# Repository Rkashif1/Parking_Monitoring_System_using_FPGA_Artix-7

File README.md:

# Parking Monitoring System Using FPGA (Artix-7)/PCB Designing

This project demonstrates a **Parking Monitoring System** implemented on an Artix-7 FPGA, designed to monitor parking spot occupancy and ensure safe parking operations. Using ultrasonic and infrared sensors, the system detects vehicle presence in each spot, with real-time status updates displayed on 7-segment displays and collision warnings triggered by a buzzer.

## Project Overview

The Parking Monitoring System leverages FPGA technology for real-time detection and monitoring of parking spaces. The FPGA processes data from multiple sensors to determine spot occupancy and prevent potential collisions. The system’s status is displayed in real-time, providing clear and accurate information on parking availability.

## Features

- **Real-Time Spot Monitoring:** Ultrasonic and infrared sensors track each parking spot’s occupancy, ensuring immediate detection of parked or vacant spaces.
- **Collision Warning System:** A buzzer alerts users to potential collisions, enhancing safety.
- **7-Segment Display for Status Updates:** Real-time parking status is displayed on multiple 7-segment displays, showing each spot’s availability.
- **Custom PCB-Level FPGA Peripheral Board:** A custom PCB board was specifically created for this project, providing a streamlined interface to connect sensors and displays directly to the FPGA. This board facilitates efficient data handling and output control, ensuring robust system performance.

## Hardware Components

- **Artix-7 FPGA:** The main controller, processing sensor inputs and managing display and buzzer outputs.
- **Ultrasonic Sensors:** Detect vehicles within parking spots, identifying occupancy.
- **Infrared Sensors:** Used for accurate vehicle detection and collision prevention.
- **7-Segment Displays:** Show each parking spot’s availability status in real-time.
- **Buzzer:** Provides an audible alert to warn against potential collisions.
- **Custom PCB Peripheral Board:** Created specifically for this project to interface the FPGA with sensors and displays, ensuring efficient data flow and control.

## Setup and Usage

1. **Hardware Setup:** Assemble the custom PCB with ultrasonic and infrared sensors connected to the Artix-7 FPGA. Configure connections to 7-segment displays and the buzzer on the PCB.
2. **FPGA Programming:** Upload the VHDL code to the FPGA for processing sensor inputs and managing output displays.
3. **Testing:** Run tests to verify real-time status display, spot detection, and collision warnings.
4. **Deployment:** Implement the system in a model parking lot setup to simulate real-world operations.

## Future Enhancements

- Integrate more advanced collision avoidance algorithms.
- Develop a mobile app to remotely monitor parking availability.
- Expand the system to manage larger parking structures.

## Team Collaboration

Each team member contributed to FPGA programming, PCB design, and sensor integration. Collaborative development ensured a robust and reliable parking monitoring solution with clear, real-time display and alerts.

## Conclusion

The Parking Monitoring System Using FPGA (Artix-7) demonstrates the use of FPGA for precise and real-time monitoring of parking spaces. With a custom PCB peripheral board specifically created for this project, collision warnings, and clear display output, this system enhances parking efficiency and safety.

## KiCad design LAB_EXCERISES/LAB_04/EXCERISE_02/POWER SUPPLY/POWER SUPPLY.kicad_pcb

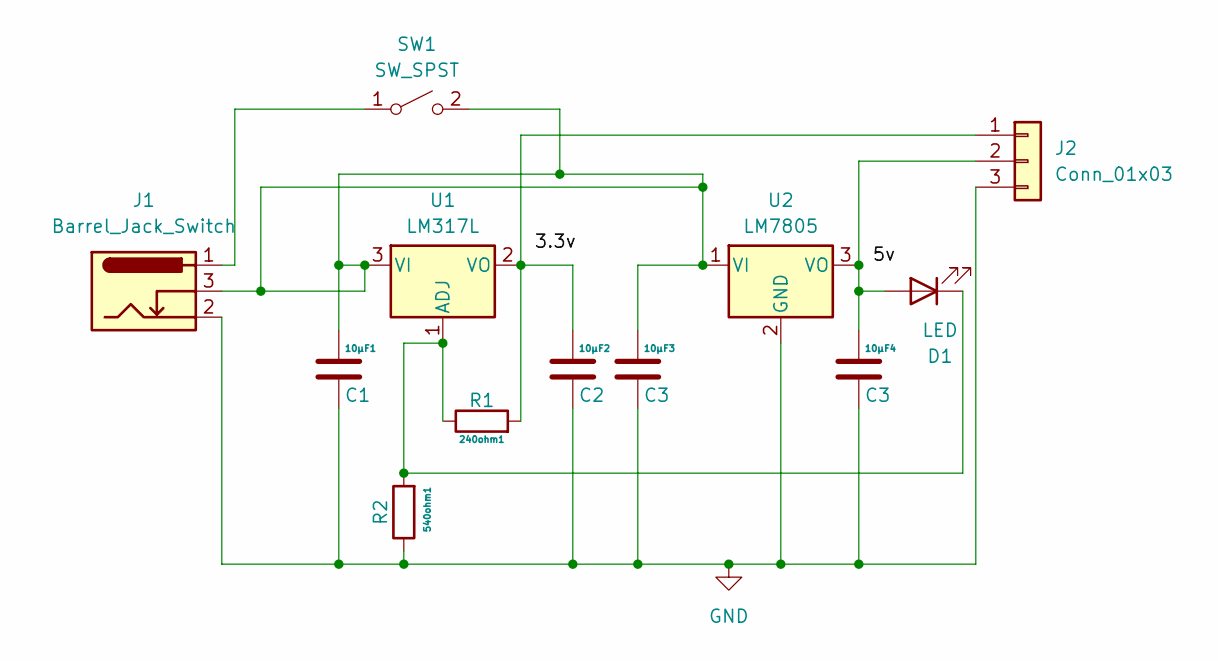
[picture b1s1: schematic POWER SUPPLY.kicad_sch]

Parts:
10µF1: C1; CP_Radial_D5.0mm_P2.00mm
10µF2: C2; CP_Radial_D5.0mm_P2.00mm
10µF3, 10µF4: C3; CP_Radial_D5.0mm_P2.00mm
240ohm1: R1; R_Axial_DIN0204_L3.6mm_D1.6mm_P5.08mm_Horizontal
540ohm1: R2; R_Axial_DIN0204_L3.6mm_D1.6mm_P5.08mm_Horizontal
D1: LED; LED_D5.0mm-4_RGB_Staggered_Pins
J1: Barrel_Jack_Switch; BarrelJack_Horizontal
J2: Conn_01x03; PinHeader_1x03_P1.00mm_Vertical
SW1: SW_SPST; SW_SPST_Omron_B3F-315x_Angled
U1: LM317L; SOT-89-3
U2: LM7805; TO-220-3_Vertical

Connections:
GND: 10µF1.2, 10µF2.2, 10µF3.2, 10µF4.2, 540ohm1.1, J1.2, J2.3, U2.2 (GND)
unnamed: 10µF4.1, D1.2 (A), J2.2, U2.3 (VO)
unnamed: 240ohm1.1, 540ohm1.2, D1.1 (K), U1.1 (ADJ)
unnamed: 10µF2.1, 240ohm1.2, J2.1, U1.2 (VO)
unnamed: J1.1, SW1.1 (A)
unnamed: 10µF1.1, 10µF3.1, J1.3, SW1.2 (B), U1.3 (VI), U2.1 (VI)

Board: 2 copper layers, 12 parts (0 on the bottom side), 6 nets, no tracks yet.

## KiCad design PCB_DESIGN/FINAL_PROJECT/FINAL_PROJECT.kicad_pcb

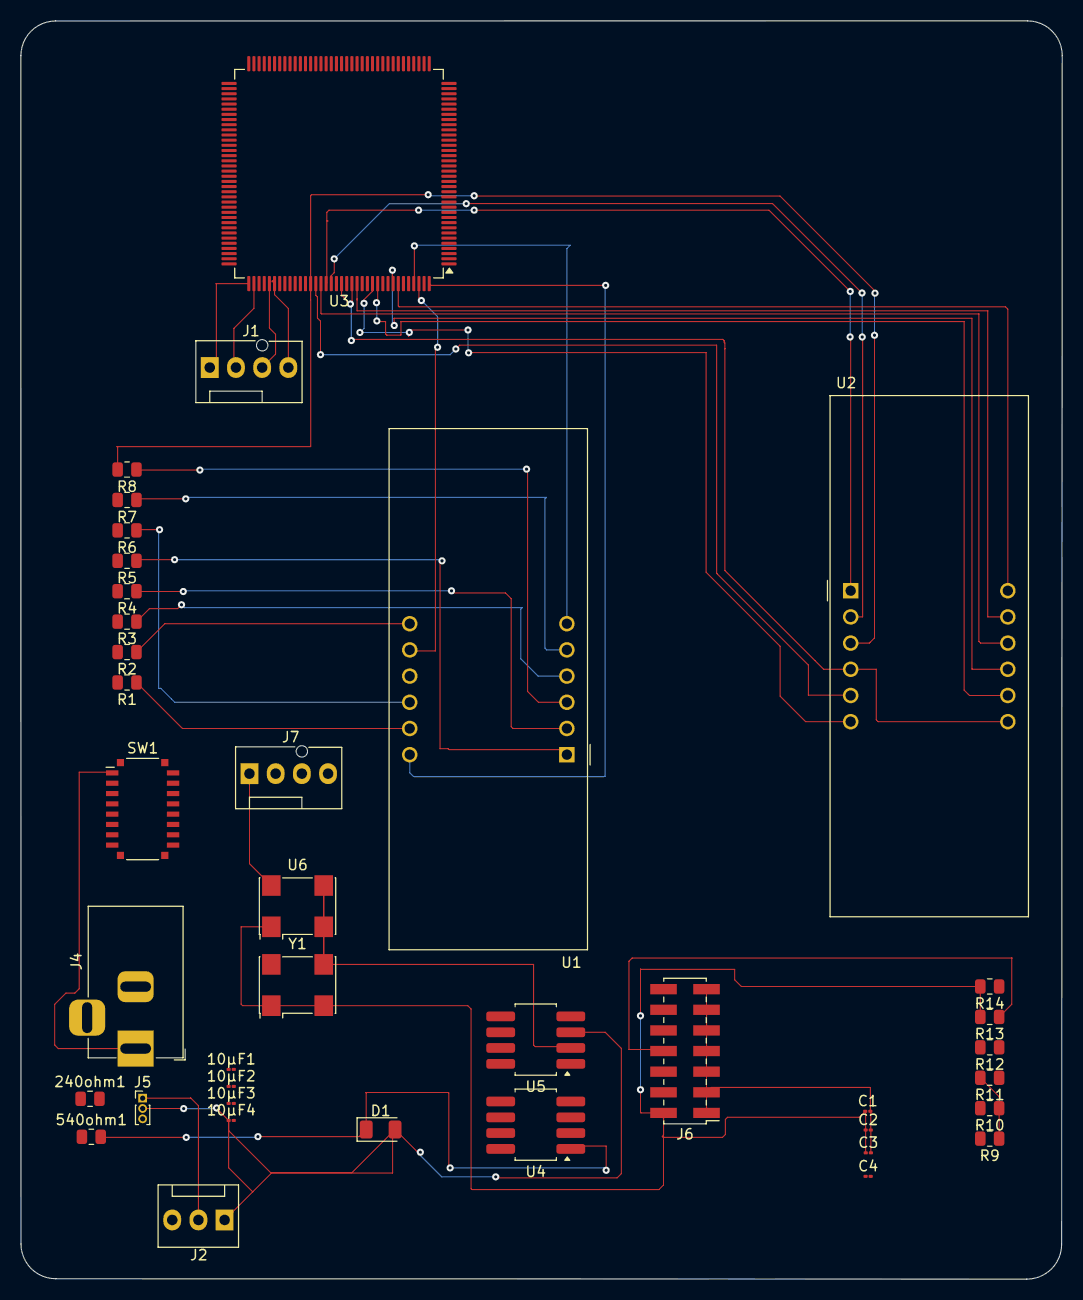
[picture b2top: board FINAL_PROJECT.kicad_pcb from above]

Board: 2 copper layers, 101.0 x 122.0 mm, 39 parts (0 on the bottom side), 39 nets.

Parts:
10µF1: C1; C_01005_0402Metric
10µF2: C2; C_01005_0402Metric
10µF3, 10µF4: C3; C_01005_0402Metric
240ohm1: R1; R_0805_2012Metric
540ohm1: R2; R_0805_2012Metric
C1, C2, C3, C4: C; C_01005_0402Metric
D1: LED; LED_1206_3216Metric
J1, J7: Conn_01x06_Pin; FanPinHeader_1x04_P2.54mm_Vertical
J2: Conn_01x02_Pin; FanPinHeader_1x03_P2.54mm_Vertical
J4: Barrel_Jack_Switch; BarrelJack_Horizontal
J5: Conn_01x03; PinHeader_1x03_P1.00mm_Vertical
J6: XILINX_JTAG; PinHeader_2x07_P2.00mm_Vertical_SMD
R1, R2, R3, R4, R5, R6, R7, R8, R10, R11, R12, R13, R14: R; R_0805_2012Metric
R9: 10k; R_0805_2012Metric
SW1: SW_SPST; SW_DIP_SPSTx08_Slide_Copal_CVS-08xB_W5.9mm_P1mm
U1, U2: CA56-12CGKWA
U3: LFXP2-5E-5TN144; TQFP-144_20x20mm_P0.5mm
U4: LM317L; SOT-223-8
U5: LM7805; SOT-223-8
U6: Oscillator_SMD_Abracon_ASV-4Pin_7.0x5.1mm
Y1: Oscillator; Oscillator_SMD_Abracon_ASV-4Pin_7.0x5.1mm

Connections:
+3.3V: C1.1, C2.1, C3.1, C4.1, J6.2 (VREF), R9.1, R10.1, R11.2, R12.2, R13.2, R14.2, U6.1 (VCCADC), Y1.1, Y1.2
/powersupply/3.3v: 10µF2.1, 240ohm1.2, J2.2, J5.1, U4.2 (VO)
/powersupply/5v: 10µF4.1, D1.2 (A), J2.1, J5.2, U5.3 (VO)
GND: 10µF1.2, 10µF2.2, 10µF3.2, 10µF4.2, 540ohm1.1, C1.2, C2.2, C3.2, C4.2, J4.2, J5.3, J6.1 (GND), J6.3 (GND), J6.5 (GND), J6.7 (GND), J6.9 (GND), J6.11 (GND), J6.13 (GND), U5.2 (GND), U6.2 (GNDADC), U6.3 (VCCBATT), Y1.3
unnamed: 240ohm1.1, 540ohm1.2, D1.1 (K), U4.1 (ADJ)
unnamed: J1.1, U3.109 (PT28B/VREF2_1)
unnamed: J1.2, U3.110 (PT28A/VREF1_1)
unnamed: J1.3, U3.113 (PT21B)
unnamed: J1.4, U3.114 (PT20B/PCLKC1_0)
unnamed: J6.6 (TCK), R12.1
unnamed: J6.10 (TDI), R14.1
unnamed: J6.8 (TDO), R13.1
unnamed: J6.4 (TMS), R11.1
unnamed: J7.1, U6.4 (TMS)
unnamed: J4.1, SW1.1 (A)
unnamed: 10µF1.1, 10µF3.1, J4.3, SW1.2 (B), U4.3 (VI), U5.1 (VI)
unnamed: U1.12 (CA1), U3.144 (PT8A/ULC_GPLLT_IN_A)
unnamed: U1.9 (CA2), U3.143 (PT7A/VREF1_0)
unnamed: U1.8 (CA3), U3.142 (PT8B/ULC_GPLLC_IN_A)
unnamed: U1.6 (CA4), U3.141 (PT7B/VREF2_0)
unnamed: R8.1, U1.3 (DPX)
unnamed: R1.1, U1.11 (a)
unnamed: R2.1, U1.7 (b)
unnamed: R3.1, U1.4 (c)
unnamed: R4.1, U1.2 (d)
unnamed: R5.1, U1.1 (e)
unnamed: R6.1, U1.10 (f)
unnamed: R7.1, U1.5 (g)
unnamed: U2.12 (CA1), U3.138 (PT9A/ULC_GPLLT_FB_A)
unnamed: U2.9 (CA2), U3.137 (PT9B/ULC_GPLLC_FB_A)
unnamed: U2.8 (CA3), U3.134 (PT13A)
unnamed: U2.6 (CA4), U3.133 (PT13B)
unnamed: R8.2, U2.3 (DPX), U3.121 (PT18B)
unnamed: R1.2, U2.11 (a), U3.130 (PT14B)
unnamed: R2.2, R3.2, U2.4 (c), U2.7 (b), U3.127 (PT16A), U3.129 (PT15B)
unnamed: R4.2, U2.2 (d), U3.125 (PT16B)
unnamed: R5.2, U2.1 (e), U3.124 (PT17A)
unnamed: R6.2, U2.10 (f), U3.123 (PT18A)
unnamed: R7.2, U2.5 (g), U3.122 (PT17B)

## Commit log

2024-05-11 HE LAB EXCERISES
2024-05-14 BCD 4 bit ADDER to 7 SEGMENT
2024-05-14 Deleted Exercise 3
2024-05-14 Changed the names
2024-06-28 Update Documentation
2024-07-24 Updated Repository
2024-07-26 Added the Remaining lab tasks
2024-07-26 Updated PCB
2024-07-26 added the labtasks
2024-07-26 Removed Folder
2024-07-26 Update Excerises
2024-11-13 Files added
